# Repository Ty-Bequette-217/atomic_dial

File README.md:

# 🚧 GitHub still in progress 🚧
# The Atomic Dial
### by Yonathan Gur, Ryan Gelston, Ty Bequette, and Cody Fuh

---

## Overview
The Atomic Dial is an open-source, haptic-enabled smart knob powered by the RP2350B architecture. It provides software-defined mechanical feedback—such as detents, virtual end-stops, and magnetic resistance—using a brushless DC motor. An adaptation of the [SmartKnob](https://github.com/scottbez1/smartknob) project by Scott Bezek, this project adapts the original device to work smoothly with the RP2350B microcontroller. The board was designed to include header pins to plug in the [Proton development board](https://ece362-purdue.github.io/proton-labs/) designed by staff for ECE 36200: Microprocessor Systems and Interfacing at Purdue University.

## Board Design & Hardware Integration
Transitioning from the original ESP32-PICO architecture to the RP2350B required a redesign of the Base PCB and hardware routing to accommodate the Proton development board. We designed a custom baseplate PCB that features female headers specifically spaced to receive the Proton board. These header pins allow anyone with a Proton board to easily recreate this project and use it with their own boards. A bulk of the work done here was carefully rerouting the signals for each of the peripherals to match the correct function needed for compatibility with the proton board (see [electronics/ProjectPinAssignments.xlsx](https://github.com/Ty-Bequette-217/atomic_dial/blob/main/electronics/ProjectPinAssignments.xlsx)).

## Firmware Architecture
To make the RP2350B drive a display, read sensors, and commutate a motor simultaneously without stuttering, the firmware is divided into distinct, non-blocking layers built on the Raspberry Pi Pico C/C++ SDK.

### AS5600 Magnetic Encoder
The AS5600 serves as the primary feedback loop for our haptic system. Mounted directly below the diametric magnet on the motor shaft, it continuously reads the absolute angular position of the knob. By feeding this high-resolution rotational data back into the RP2350B, the firmware can calculate exact phase angles and trigger localized spikes in motor torque, allowing the user to feel physical "clicks" entirely generated by software.

### GC9A01 Round LCD
The primary user interface is driven by a 1.28-inch GC9A01 circular LCD, which receives data over the RP2350B's hardware SPI bus to maintain a high framerate.

#### Initialization for GC9A01
Bringing up the GC9A01 requires a precise sequence of initialization commands sent over SPI. The firmware configures the display out of sleep mode, sets the pixel format to 16-bit color (RGB565), defines the memory access control for correct screen orientation, and establishes the circular column and row address windows. A hardware reset line is toggled on boot to ensure the display controller starts in a known, clean state before accepting pixel data.

#### Inclusion of LVGL C Library
To handle the complex graphics, menus, and animations without writing pixel-level drawing routines from scratch, we integrated the [LVGL (Light and Versatile Graphics Library)](https://lvgl.io/). LVGL operates using internal draw buffers. We implemented a custom `disp_flush` callback function that takes LVGL's rendered buffer blocks and pushes them over the SPI bus to the GC9A01. This allows us to create smooth, professional-looking UI dials and scrolling menus that react in real-time to the motor encoder.

### TMC6300 Motor Driver
The physical haptic feedback is generated by a gimbal brushless DC motor driven by the TMC6300. The RP2350B uses its hardware PWM slices to output precisely timed, 3-phase sinusoidal waveforms (Space Vector PWM) to the motor coils. Because the PWM generation is handled by hardware timers rather than the main CPU loop, the motor commutation remains completely jitter-free even while the processor is busy rendering graphics or reading sensors.

### HX711 Load Cell Amplifier
To add a "push-to-click" dimension to the dial, we integrated SMD resistors acting as load cells monitored by an HX711 24-bit ADC. When the HX711 outout decreases below the threshold, a push is registered and changes the state of the device.

### LDR monitoring for LCD Brightness
To optimize visibility and power consumption, the dial features dynamic backlight adjustment. A Light Dependent Resistor (LDR) acts as an ambient light sensor, read continuously by the RP2350B's internal 12-bit ADC. The firmware maps these raw ADC values to a duty cycle percentage, which is then fed into a hardware PWM slice driving the `LCD_BACKLIGHT` pin. This ensures the display dims in dark rooms and ramps to full brightness in heavily lit environments without any manual user intervention.

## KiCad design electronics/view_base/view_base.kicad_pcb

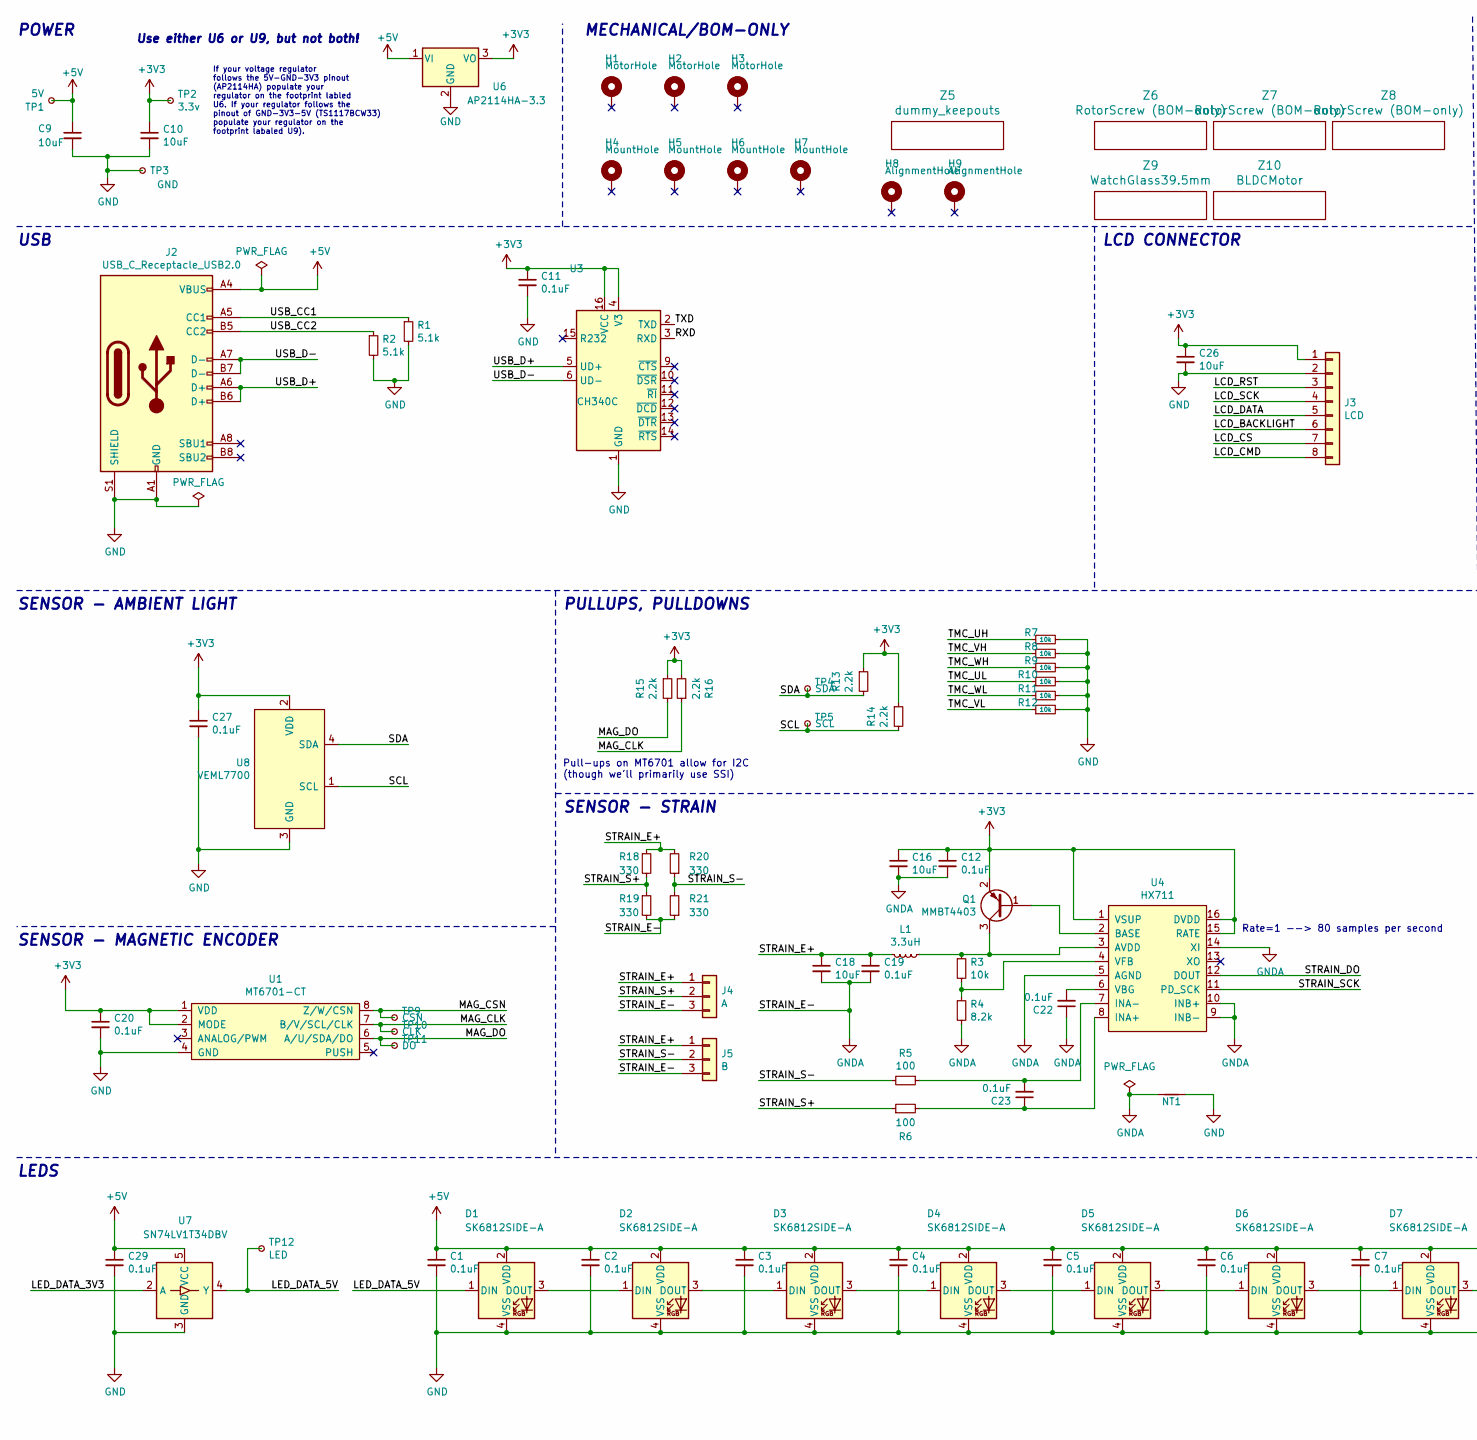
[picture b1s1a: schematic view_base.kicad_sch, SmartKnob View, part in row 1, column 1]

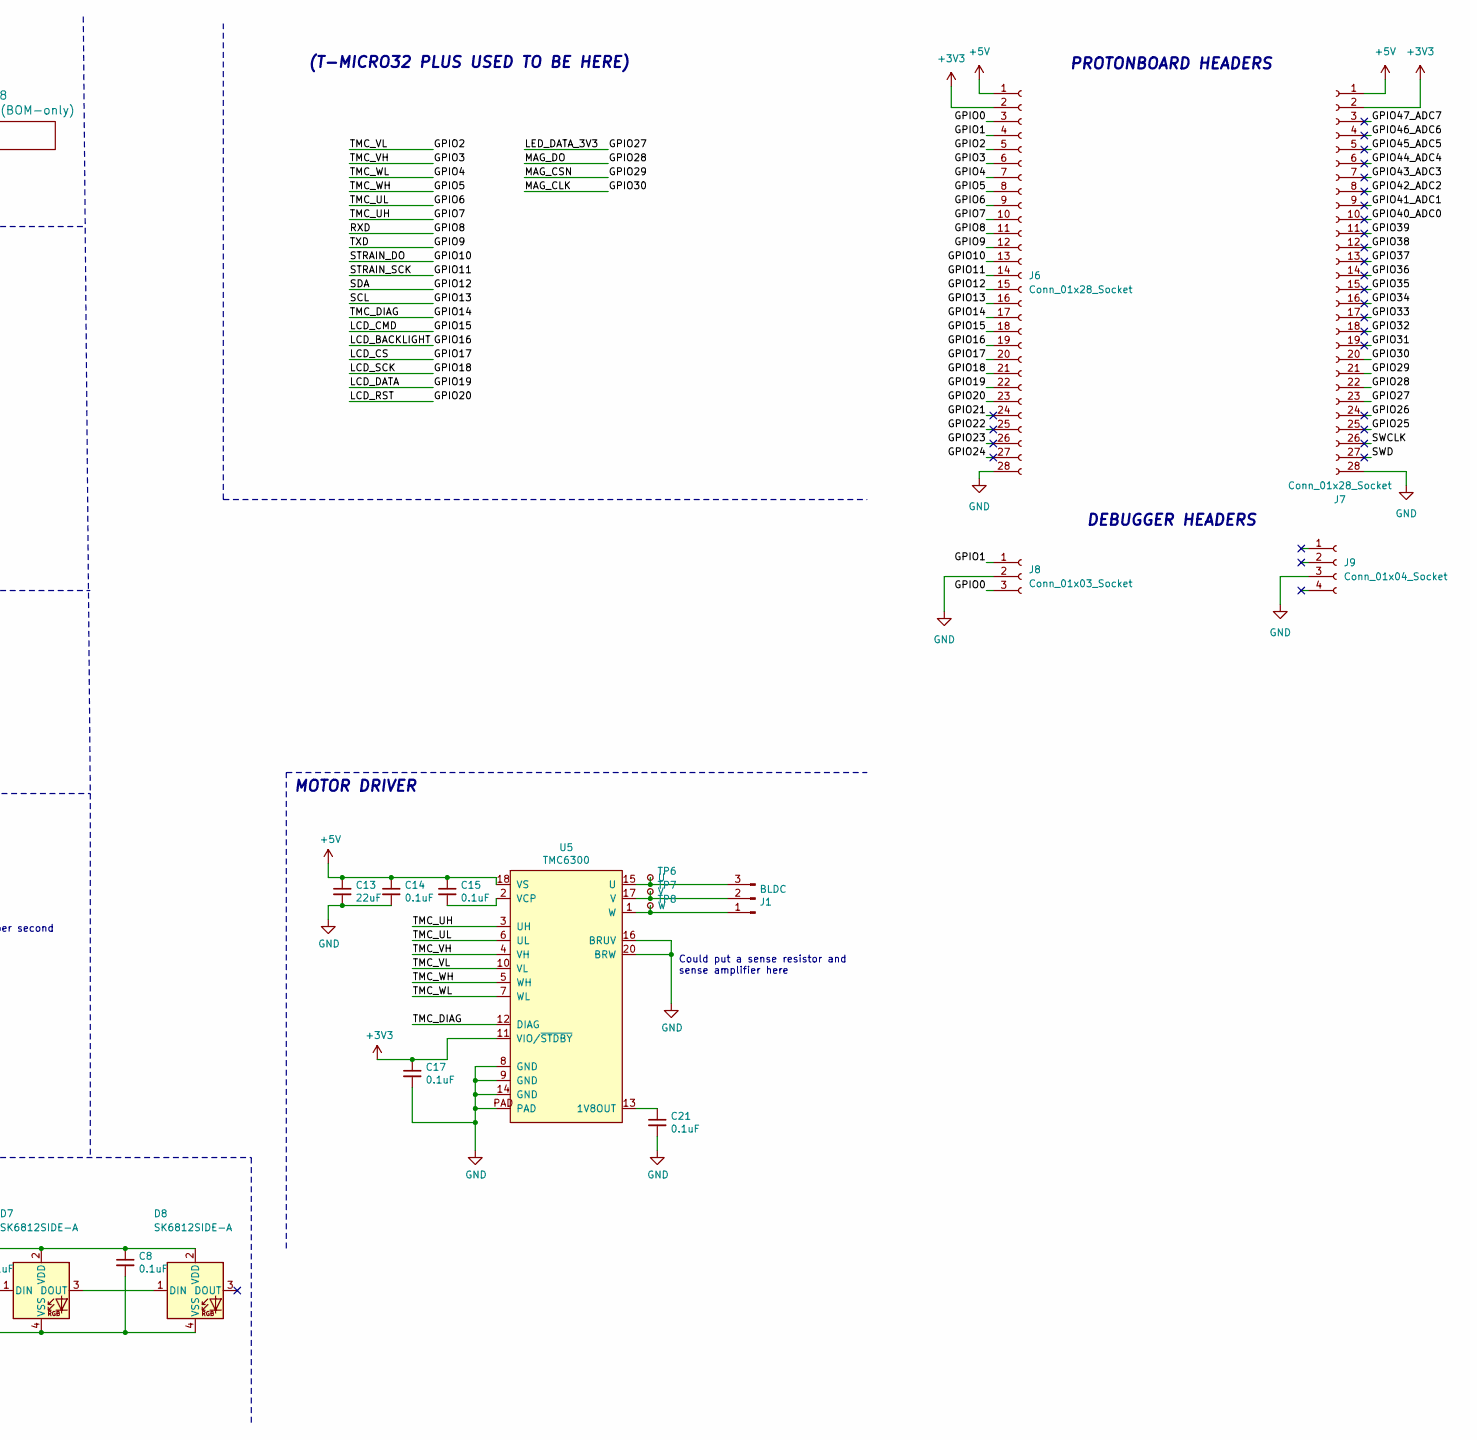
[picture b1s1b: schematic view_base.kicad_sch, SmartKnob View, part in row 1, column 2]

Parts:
C1, C2, C3, C4, C5, C6, C7, C8, C11, C12, C14, C15, C17, C19, C20, C21, C22, C23, C27, C29: 0.1uF; C_0603_1608Metric; LCSC C1591
C9, C10, C16, C18, C26: 10uF; C_0805_2012Metric; LCSC C2922480
C13: 22uF; C_0805_2012Metric; LCSC C98190
D1, D2, D3, D4, D5, D6, D7, D8: SK6812SIDE-A; SK6812-SIDE-A; Digikey 1528-4691-ND
H1, H2, H3: MotorHole; MountingHole_M1.6; LCSC C2931389
H4, H5, H6, H7: MountHole; MountingHole_2.2mm_M2_ISO7380_Pad_NonVirtual; LCSC C2911210 or C2911532 (screw), C2961595 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
H8, H9: AlignmentHole; MountingHole_2.2mm_M2_ISO7380_Pad_NonVirtual
J1: BLDC; 532610371; LCSC C293630
J2: USB_C_Receptacle_USB2.0; USB4510_NoPaste; LCSC C428463
J3: LCD; SolderPads_2mm_8
J4: A; SolderPads_2mm_3_STRAIN
J5: B; SolderPads_2mm_3_STRAIN
J6, J7: Conn_01x28_Socket; PinSocket_1x28_P2.54mm_Vertical
J8: Conn_01x03_Socket; PinSocket_1x03_P2.54mm_Vertical
J9: Conn_01x04_Socket; PinSocket_1x04_P2.54mm_Vertical
L1: 3.3uH; L_0805_2012Metric; LCSC C307744
NT1: NetTie_2; NetTie-2_SMD_Pad0.5mm
Q1: MMBT4403; SOT-23; LCSC C78864
R1, R2: 5.1k; R_0603_1608Metric; LCSC C105580
R3, R7, R8, R9, R10, R11, R12: 10k; R_0603_1608Metric; LCSC C98220
R4: 8.2k; R_0603_1608Metric; LCSC C114637
R5, R6: 100; R_0603_1608Metric; LCSC C319953
R13, R14, R15, R16: 2.2k; R_0603_1608Metric; LCSC C4190
R18, R19, R20, R21: 330; R_2512_6332Metric; LCSC C19866
TP1: 5V; TestPoint_Pad_D2.0mm_ValueSilk
TP2: 3.3v; TestPoint_Pad_D2.0mm_ValueSilk
TP3: GND; TestPoint_Pad_D2.0mm_ValueSilk
TP4: SDA; TestPoint_Pad_D2.0mm_ValueSilk
TP5: SCL; TestPoint_Pad_D2.0mm_ValueSilk
TP6: U; TestPoint_Pad_D2.0mm_ValueSilk
TP7: V; TestPoint_Pad_D2.0mm_ValueSilk
TP8: W; TestPoint_Pad_D2.0mm_ValueSilk
TP9: CSN; TestPoint_Pad_D2.0mm_ValueSilk
TP10: CLK; TestPoint_Pad_D2.0mm_ValueSilk
TP11: DO; TestPoint_Pad_D2.0mm_ValueSilk
TP12: LED; TestPoint_Pad_D2.0mm_ValueSilk
U1: MT6701-CT; SOIC-8_3.9x4.9mm_P1.27mm; LCSC C2856764, or C3003196
U3: CH340C; SOIC-16_3.9x9.9mm_P1.27mm; LCSC C84681
U4: HX711; SOIC-16_3.9x9.9mm_P1.27mm; LCSC C43656
U5: TMC6300; QFN-20-1EP_3x3mm_P0.4mm_EP1.65x1.65mm_ThermalVias_LargerVia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; Digikey TMC6300-LA-T
U6: AP2114HA-3.3; SOT-223-3_TabPin2_InGndOut; LCSC C460314
U7: SN74LV1T34DBV; SOT-23-5; LCSC C100024
U8: VEML7700; VEML7700-TOP; Digikey VEML7700-TT
Z5: dummy_keepouts; ViewKeepouts3d
Z6, Z7, Z8: RotorScrew (BOM-only); bom_only_no_pin
Z9: WatchGlass39.5mm; bom_only_no_pin
Z10: BLDCMotor; bom_only_no_pin

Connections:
+3V3: C10.1, C11.1, C12.1, C16.1, C17.1, C20.1, C26.1, C27.1, J3.1, J6.2, J7.2, Q1.2 (E), R13.1, R14.1, R15.1, R16.2, TP2.1, U1.1 (VDD), U1.2 (MODE), U3.4 (V3), U3.16 (VCC), U4.1 (VSUP), U4.15 (RATE), U4.16 (DVDD), U5.11 (VIO/~STDBY), U6.3 (VO), U8.2 (VDD); also elsewhere on the board
+5V: C1.1, C2.1, C3.1, C4.1, C5.1, C6.1, C7.1, C8.1, C9.1, C13.1, C14.1, C15.1, C29.1, D1.2 (VDD), D2.2 (VDD), D3.2 (VDD), D4.2 (VDD), D5.2 (VDD), D6.2 (VDD), D7.2 (VDD), D8.2 (VDD), J2.A4 (VBUS), J2.A9 (VBUS), J2.B4 (VBUS), J2.B9 (VBUS), J6.1, J7.1, TP1.1, U5.18 (VS), U6.1 (VI), U7.5 (VCC); also elsewhere on the board
/GPIO0: J6.3, J8.3
/GPIO1: J6.4, J8.1
/GPIO2: J6.5, R12.1, U5.10 (VL)
/GPIO3: J6.6, R8.1, U5.4 (VH)
/GPIO4: J6.7, R11.1, U5.7 (WL)
/GPIO5: J6.8, R9.1, U5.5 (WH)
/GPIO6: J6.9, R10.1, U5.6 (UL)
/GPIO7: J6.10, R7.1, U5.3 (UH)
/GPIO8: J6.11, U3.3 (RXD)
/GPIO9: J6.12, U3.2 (TXD)
/GPIO10: J6.13, U4.12 (DOUT)
/GPIO11: J6.14, U4.11 (PD_SCK)
/GPIO12: J6.15, R13.2, TP4.1, U8.4 (SDA)
/GPIO13: J6.16, R14.2, TP5.1, U8.1 (SCL)
/GPIO14: J6.17, U5.12 (DIAG)
/GPIO15: J3.8, J6.18
/GPIO16: J3.6, J6.19
/GPIO17: J3.7, J6.20
/GPIO18: J3.4, J6.21
/GPIO19: J3.5, J6.22
/GPIO20: J3.3, J6.23
/GPIO21: J6.24
/GPIO22: J6.25
/GPIO23: J6.26
/GPIO24: J6.27
/GPIO25: J7.25
/GPIO26: J7.24
/GPIO27: J7.23, U7.2 (A)
/GPIO28: J7.22, R15.2, TP11.1, U1.6 (A/U/SDA/DO)
/GPIO29: J7.21, TP9.1, U1.8 (Z/W/CSN)
/GPIO30: J7.20, R16.1, TP10.1, U1.7 (B/V/SCL/CLK)
/GPIO31: J7.19
/GPIO32: J7.18
/GPIO33: J7.17
/GPIO34: J7.16
/GPIO35: J7.15
/GPIO36: J7.14
/GPIO37: J7.13
/GPIO38: J7.12
/GPIO39: J7.11
/GPIO40_ADC0: J7.10
/GPIO41_ADC1: J7.9
/GPIO42_ADC2: J7.8
/GPIO43_ADC3: J7.7
/GPIO44_ADC4: J7.6
/GPIO45_ADC5: J7.5
/GPIO46_ADC6: J7.4
/GPIO47_ADC7: J7.3
/LED_DATA_5V: D1.1 (DIN), TP12.1, U7.4 (Y)
/STRAIN_E+: C18.1, C19.1, J4.1, J5.1, L1.2, R18.1, R20.2
/STRAIN_S+: J4.2, R6.1, R18.2, R19.1
/STRAIN_S-: J5.2, R5.2, R20.1, R21.2
/SWCLK: J7.26
/SWD: J7.27
/USB_CC1: J2.A5 (CC1), R1.1
/USB_CC2: J2.B5 (CC2), R2.1
/USB_D+: J2.A6 (D+), J2.B6 (D+), U3.5 (UD+)
/USB_D-: J2.A7 (D-), J2.B7 (D-), U3.6 (UD-)
GND: C1.2, C2.2, C3.2, C4.2, C5.2, C6.2, C7.2, C8.2, C9.2, C10.2, C11.2, C13.2, C14.2, C17.2, C20.2, C21.2, C26.2, C27.2, C29.2, D1.4 (VSS), D2.4 (VSS), D3.4 (VSS), D4.4 (VSS), D5.4 (VSS), D6.4 (VSS), D7.4 (VSS), D8.4 (VSS), J2.A1 (GND), J2.A12 (GND), J2.B1 (GND), J2.B12 (GND), J2.S1 (SHIELD), J3.2, J6.28, J7.28, J8.2, J9.3, NT1.2, R1.2, R2.2, R7.2, R8.2, R9.2, R10.2, R11.2, R12.2, TP3.1, U1.4 (GND), U3.1 (GND), U5.8 (GND), U5.9 (GND), U5.14 (GND), U5.16 (BRUV), U5.20 (BRW), U5.PAD, U6.2 (GND), U7.3 (GND), U8.3 (GND); also elsewhere on the board
GNDA: C12.2, C16.2, C18.2, C19.2, C22.1, J4.3, J5.3, NT1.1, R4.2, R19.2, R21.1, U4.5 (AGND), U4.9 (INB-), U4.10 (INB+), U4.14 (XI)
unnamed: D1.3 (DOUT), D2.1 (DIN)
unnamed: D2.3 (DOUT), D3.1 (DIN)
unnamed: D3.3 (DOUT), D4.1 (DIN)
unnamed: D4.3 (DOUT), D5.1 (DIN)
unnamed: D5.3 (DOUT), D6.1 (DIN)
unnamed: D6.3 (DOUT), D7.1 (DIN)
unnamed: D7.3 (DOUT), D8.1 (DIN)
unnamed: J1.1, TP8.1, U5.1 (W)
unnamed: J1.2, TP7.1, U5.17 (V)
unnamed: J1.3, TP6.1, U5.15 (U)
unnamed: Q1.1 (B), U4.2 (BASE)
unnamed: L1.1, Q1.3 (C), R3.1, U4.3 (AVDD)
unnamed: C23.1, R6.2, U4.8 (INA+)
unnamed: C23.2, R5.1, U4.7 (INA-)
unnamed: C22.2, U4.6 (VBG)
unnamed: R3.2, R4.1, U4.4 (VFB)
unnamed: C21.1, U5.13 (1V8OUT)
unnamed: C15.2, U5.2 (VCP)

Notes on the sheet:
POWER
Could put a sense resistor and sense amplifier here
PROTONBOARD HEADERS
(T-MICRO32 PLUS USED TO BE HERE)
If your voltage regulator follows the 5V-GND-3V3 pinout (AP2114HA) populate your regulator on the footprint labled U6. If your regulator follows the pinout of GND-3V3-5V (TS1117BCW33) populate your regulator on the footprint labaled U9).
SENSOR - MAGNETIC ENCODER
MOTOR DRIVER
MECHANICAL/BOM-ONLY
Pull-ups on MT6701 allow for I2C (though we'll primarily use SSI)
Use either U6 or U9, but not both!
Rate=1 --> 80 samples per second
SENSOR - AMBIENT LIGHT
USB
DEBUGGER HEADERS
SENSOR - STRAIN
LEDS
PULLUPS, PULLDOWNS
LCD CONNECTOR

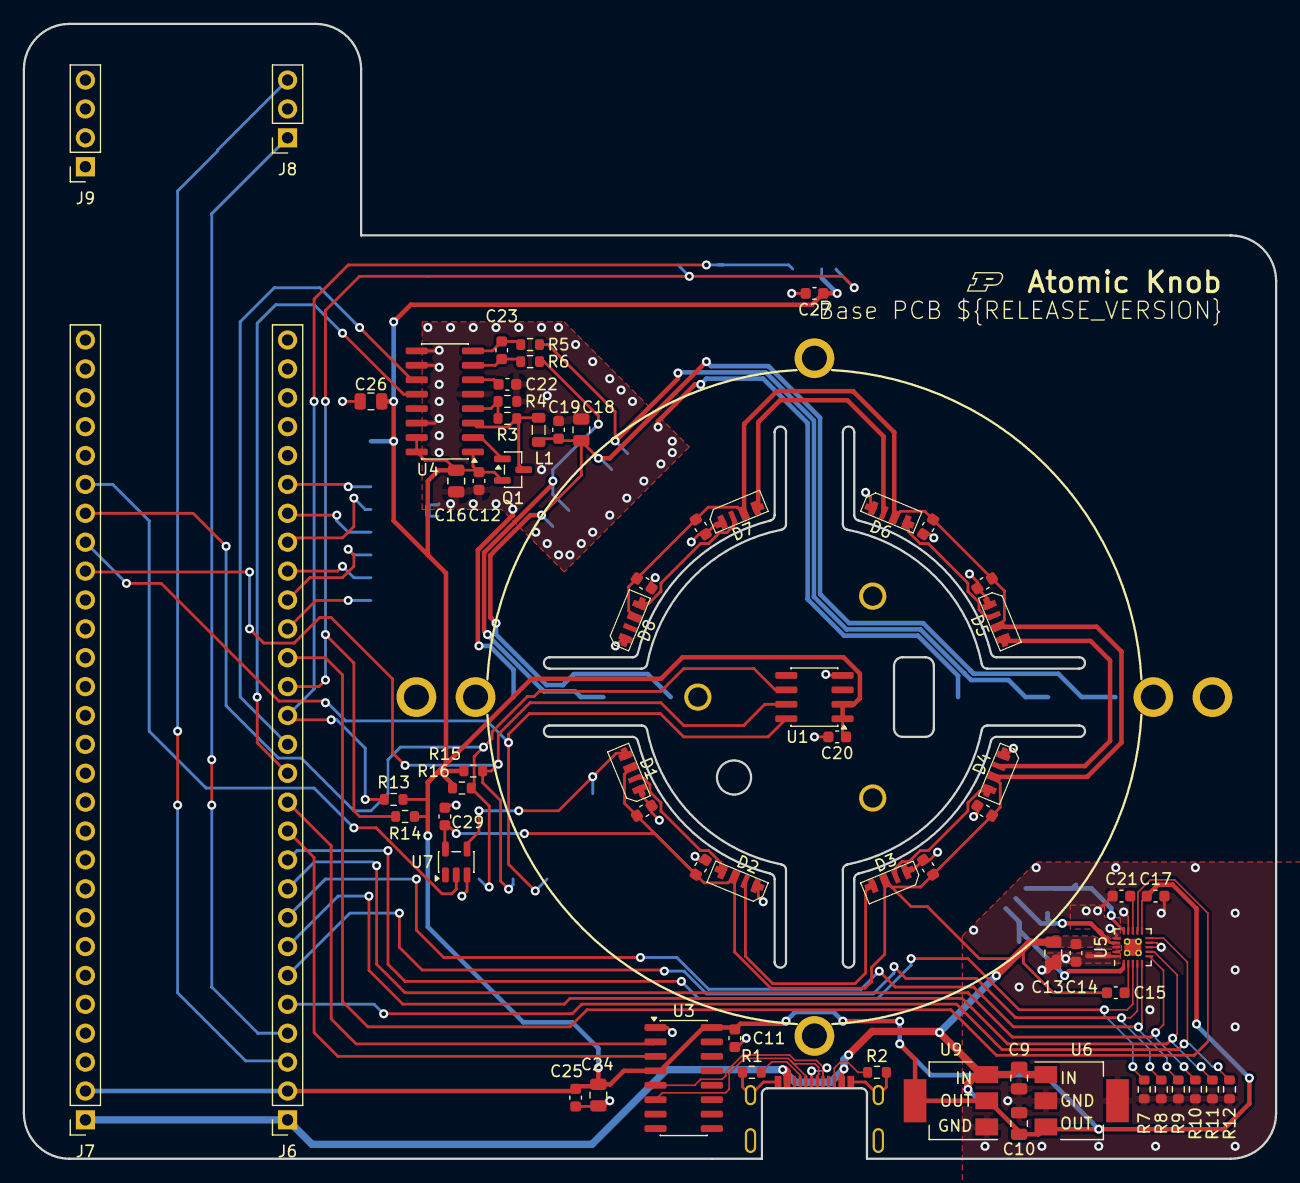
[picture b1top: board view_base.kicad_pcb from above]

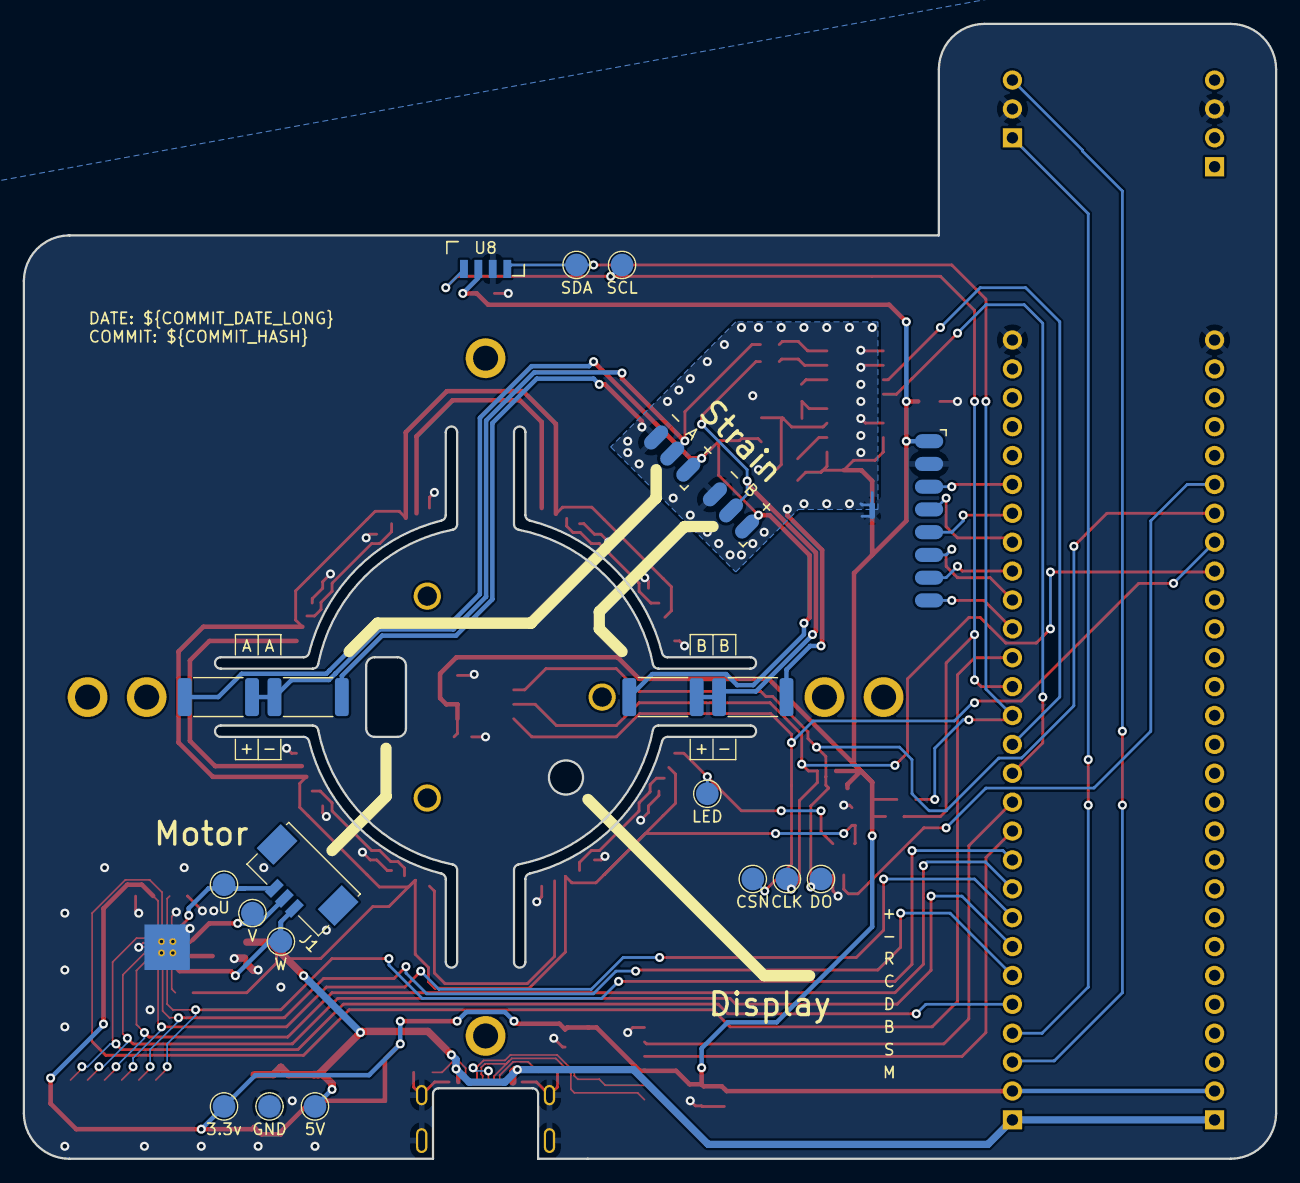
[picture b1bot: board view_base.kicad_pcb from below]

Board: 2 copper layers, 110.1 x 99.8 mm, 103 parts (22 on the bottom side), 55 nets.

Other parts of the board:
C24: 10uF; C_0805_2012Metric
C25: 0.1uF; C_0603_1608Metric
U9: TS1117BCW33_RPG; SOT-223-3_TabPin2_GndOutIn

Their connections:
+3V3: C24.1, C25.1, U9.2 (Output); also elsewhere on the board
+5V: U9.3 (Input); also elsewhere on the board
GND: C24.2, C25.2, U9.1 (GND); also elsewhere on the board

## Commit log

2026-03-04 init kicad files
2026-03-09 sunday work
2026-03-09 Adding pin assignment spreadsheet
2026-03-28 filled out excel with pin mappings using gemini (pls validate if possible)
2026-03-28 changed GPIO for UL/UH to accomodate debugger TX and RX
2026-03-28 initial layout
2026-03-28 more layout and simplification
2026-03-28 added RP 2350 pin table
2026-03-29 Reassigned pins in excel sheet
2026-03-30 more layout
2026-03-31 Python Example and Software
2026-03-31 Firmware/Must calibrate everything before testing
2026-03-31 I added the programming but there are two .ini files. Please advise to change these and the current code runs on my user. You need to change this or use my computer to flash the smartknob
2026-03-31 worked on some routing and edited the ground plane, feel free to revert just wanted to mess with it
2026-03-31 got rid of some ground traces in favor of using plane
2026-04-01 finished layout
2026-04-02 redid routing and schematic to match GPIO pins from excel
2026-04-03 consult TA about layout
2026-04-03 Changed TMC6300 footprint to make vias into thermal reliefs to get rid of drc, added in project title and purdue P
2026-04-16 Creating folder for build from ground 0
2026-04-16 added LDR pin in excel
2026-04-16 fixed things for ldr pin
2026-04-17 got rid of unneccessary files
2026-04-17 got rid of more unnecessary files
2026-04-17 a few more files removed
2026-04-17 added updated rebuilt folder (hopefully with working git submodule for lvgl support)
2026-04-17 made ldr and lcd things functional with seperate display.c file
2026-04-17 test file. need to construct wheatstone bridge
    debugging and calibration required. This code reads the analog voltage value on the assigned pin and supposed hx711 high and low output. We need to calibrate the amplifier by "taring" to the load cel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
2026-04-18 finished making HX711 code that works with wheatstone bridge (1k resistors with 1k pot)
2026-04-18 Adding support to change states with button on the Proton
2026-04-18 disregard earlier commit. Remembered I already made the button change states inside of the state machine file
2026-04-18 Ring color should now change based on state!
2026-04-18 updated encoder pins since it is now i2c
2026-04-18 adding ported library for encoder
2026-04-18 supporting functions for as5600 mag encoder
2026-04-19 Adding support for simple FOC to control the motor and updated the state machine system to support tracking of the position more cleanly.
2026-04-19 It's absolutely tweaking out with alleged problems but the thing compiles with platformio
2026-04-19 started with motor control stuff
2026-04-19 moved hx711.c and hx711.h to rebuilt folder from hx711 test folder
2026-04-22 added personal test folder for Yonathan
2026-04-22 Adding motor control
2026-04-22 added motor folder
2026-04-22 added motor folder and most recent code
2026-04-22 added in hx711 modules to motor folder
2026-04-22 all checkoffs done!
2026-04-22 got rid of rebuilt_playground and renamed rebuilt as old since motor is our main working folder
2026-04-22 cleaned up main.c, added display.h and display.c in motor folder (untested on actual hardware)
2026-04-22 added in some changes to some .h and .c files with c++ sections to get rid of warnings/errors
2026-04-22 Started writing in README.md
2026-04-22 moved pin assignment excel into electronics folder
2026-04-22 Added Links to proton and pin assignment excel
2026-04-29 Fine tuning of detent behavior and UI
2026-04-29 Including new ON/OFF mode. Partially working,
2026-04-29 Added changes to fix mode skipping and angle drift following calibration
2026-04-29 added Yonathan work folder

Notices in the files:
parts and their libraries:
Copyright 2021 Accelerated Designs. All rights reserved.
